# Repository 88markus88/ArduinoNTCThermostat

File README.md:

# ArduinoNTCThermostat
This project is an Arduino based Thermostat for universal use. I put it together rather quick&dirty since I needed a simple thermostat, and I could not find one that fit my needs...
The project contains the Arduino code and the KiCad files for the board.

I ended up with a rather generic setup, that may be of use to others. The thermostat is intended to be used standalone in 12V or 24 V environments. It's settings for cooling or heating mode, for the target temperature and the hysteresis can be set without recompilation using a bridge (heating/cooling) and DIP switches (target temperature and hysteresis). A relay is fitted that can switch up to 250V and 10A.
A SSD1306 compatible OLED display can be fitted as an option to display detailed information.

## Features:
- Temperature measurement is done via a 10K NTC sensor
- Powered using an efficient DCDC converter (Traco TSR 1-2450E pin compatible to 7805) for operation in range of 7-36 V DC. The thermostat can easily operate in 12 or 24 V installations.
- Set for heating or cooling operation with a bridge
- Set target temperature fron 0 to 254 °C in 2°C steps via DIP switches
- Set hysteresis from 0 to 14 °C in 2°C steps via DIP switches
- 250V 10A relay. PCB design supports up to 10 A
- 2 LEDs: power indicator and switch indicator
- Optional OLED display via I2C

## PCB
The PCB has been designed in Kicad. Kicad files are included in this repository, also the Gerber files that can directly be used to order the PCBs

## Parts List
- PCB: Gerber files are attached
- Arduino Pro Micro (with socket, if desired)
- Transistor BC547
- Electrolyte Capacitor 47 uF / 25V
- Tantal Capacitor 100 nF
- Opto Coupler LTV 817
- 2 Diodes 1N4001 or 1N4004
- 2 LEDs
- Power via DCDC  Traco TSR 1-2450E, alternatively 7850
- 10x DIP Switch
- Screw Terminals 5.08 mm pitch: 2x 2, 1x 3 connections
- Relay Songle SRD-05VDC-SL-C
- Resistors: 200, 470 and 2 x 10K Ohm
- NTC 10K
- OLED Display with SSD1306 controller (optional)
- Housing

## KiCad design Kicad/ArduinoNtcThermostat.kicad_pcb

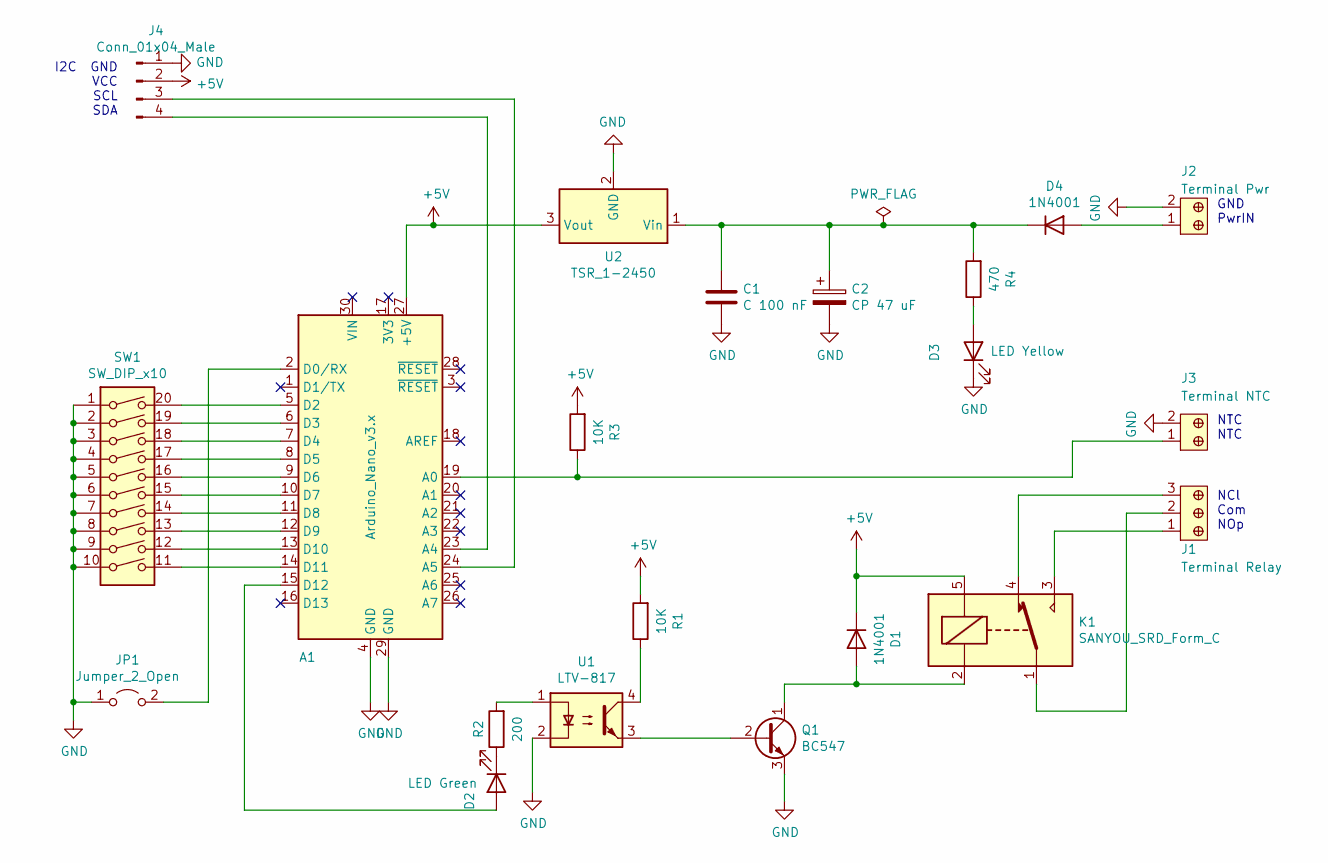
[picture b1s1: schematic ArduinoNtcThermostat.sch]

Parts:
A1: Arduino_Nano_v3.x; Arduino_Nano_WithMountingHoles
C1: C 100 nF; C_Disc_D4.3mm_W1.9mm_P5.00mm
C2: CP 47 uF; CP_Radial_D10.0mm_P5.00mm
D1, D4: 1N4001; D_DO-41_SOD81_P10.16mm_Horizontal
D2: LED Green; LED_D5.0mm
D3: LED Yellow; LED_D5.0mm
J1: Terminal Relay; TERM_BLOCK_1x3_P5.08MM; MPN OSTTC032162; Digi-Key_PN ED2610-ND
J2: Terminal Pwr; Term_Block_1x2_P5.08MM; MPN OSTTC022162; Digi-Key_PN ED2609-ND
J3: Terminal NTC; Term_Block_1x2_P5.08MM; MPN OSTTC022162; Digi-Key_PN ED2609-ND
J4: Conn_01x04_Male; PinHeader_1x04_P2.54mm_Vertical
JP1: Jumper_2_Open; PinHeader_1x02_P2.54mm_Vertical
K1: SANYOU_SRD_Form_C; Relay_SPDT_SANYOU_SRD_Series_Form_C
Q1: BC547; TO-92_HandSolder
R1, R3: 10K; R_Axial_DIN0207_L6.3mm_D2.5mm_P10.16mm_Horizontal
R2: 200; R_Axial_DIN0207_L6.3mm_D2.5mm_P10.16mm_Horizontal
R4: 470; R_Axial_DIN0207_L6.3mm_D2.5mm_P10.16mm_Horizontal
SW1: SW_DIP_x10; DIP-20_W7.62mm
U1: LTV-817; DIP-4_W7.62mm
U2: TSR_1-2450; Converter_DCDC_TRACO_TSR-1_THT

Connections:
+5V: A1.27 (+5V), D1.1 (K), J4.2, K1.5, R1.2, R3.2, U2.3 (Vout)
GND: A1.4 (GND), A1.29 (GND), C1.2, C2.2, D3.1 (K), J2.2, J3.2, J4.1, JP1.1 (A), Q1.3 (E), SW1.1, SW1.2, SW1.3, SW1.4, SW1.5, SW1.6, SW1.7, SW1.8, SW1.9, SW1.10, U1.2, U2.2 (GND)
unnamed: A1.2 (D0/RX), JP1.2 (B)
unnamed: A1.5 (D2), SW1.20
unnamed: A1.6 (D3), SW1.19
unnamed: A1.7 (D4), SW1.18
unnamed: A1.8 (D5), SW1.17
unnamed: A1.9 (D6), SW1.16
unnamed: A1.10 (D7), SW1.15
unnamed: A1.11 (D8), SW1.14
unnamed: A1.12 (D9), SW1.13
unnamed: A1.13 (D10), SW1.12
unnamed: A1.14 (D11), SW1.11
unnamed: A1.15 (D12), D2.2 (A)
unnamed: A1.19 (A0), J3.1, R3.1
unnamed: A1.23 (A4), J4.4
unnamed: A1.24 (A5), J4.3
unnamed: C1.1, C2.1, D4.1 (K), R4.2, U2.1 (Vin)
unnamed: D1.2 (A), K1.2, Q1.1 (C)
unnamed: D2.1 (K), R2.1
unnamed: D3.2 (A), R4.1
unnamed: D4.2 (A), J2.1
unnamed: J1.1, K1.3
unnamed: J1.2, K1.1
unnamed: J1.3, K1.4
unnamed: Q1.2 (B), U1.3
unnamed: R1.1, U1.4
unnamed: R2.2, U1.1

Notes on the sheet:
I2C GND VCC SCL SDA
NCl Com NOp
NTC NTC
GND PwrIN

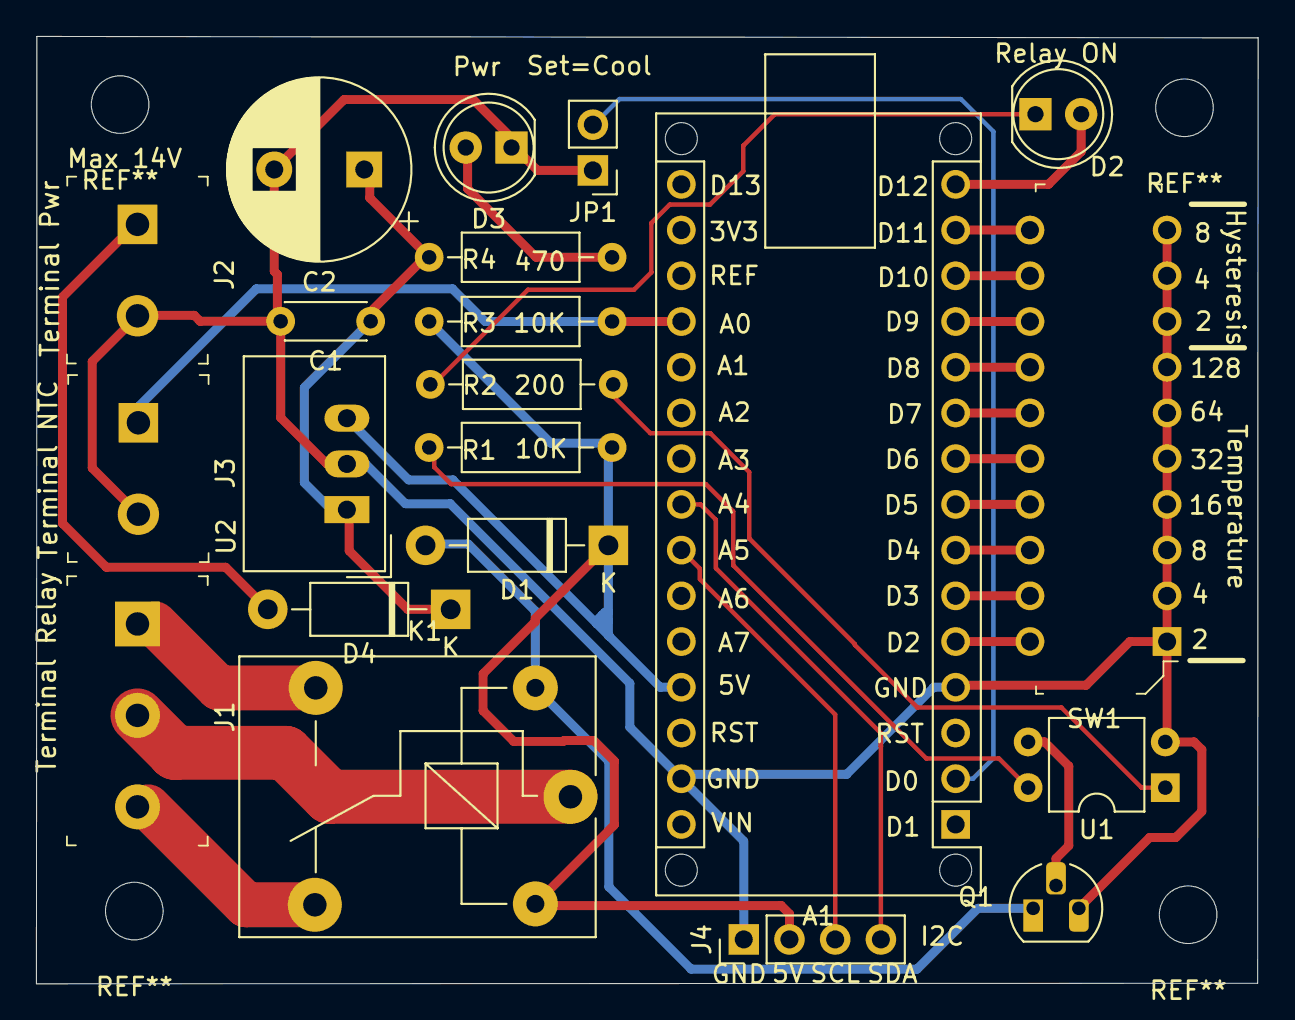
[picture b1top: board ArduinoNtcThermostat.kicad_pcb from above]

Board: 2 copper layers, 67.9 x 52.6 mm, 21 parts (0 on the bottom side), 28 nets.

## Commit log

2021-11-30 Initial Commit of Arduino NTC Thermostat - V0.03
2021-11-30 Initial Commit with V0.03
2021-11-30 V0.03
2021-12-01 Pictures of PCB added
2021-12-01 Update README.md
    Added PCB pictures to Readme.md
2021-12-01 Update README.md
    Upgraded description in readme.md
2022-02-12 Updated ESP32 platform to 3.5.0 (still with Arduino 1.0.6)
2023-11-20 Update README.md
    Added parts list
2023-11-20 Update README.md
    completed parts list
